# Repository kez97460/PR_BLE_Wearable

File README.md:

# Projet de recherche - beacon BLE wearable

Projet de recherche de Lïam Lotte et Kézia Marcou - mineure E&E. 

Vous trouverez le rapport du projet en .pdf à ce [lien](project_report.pdf).

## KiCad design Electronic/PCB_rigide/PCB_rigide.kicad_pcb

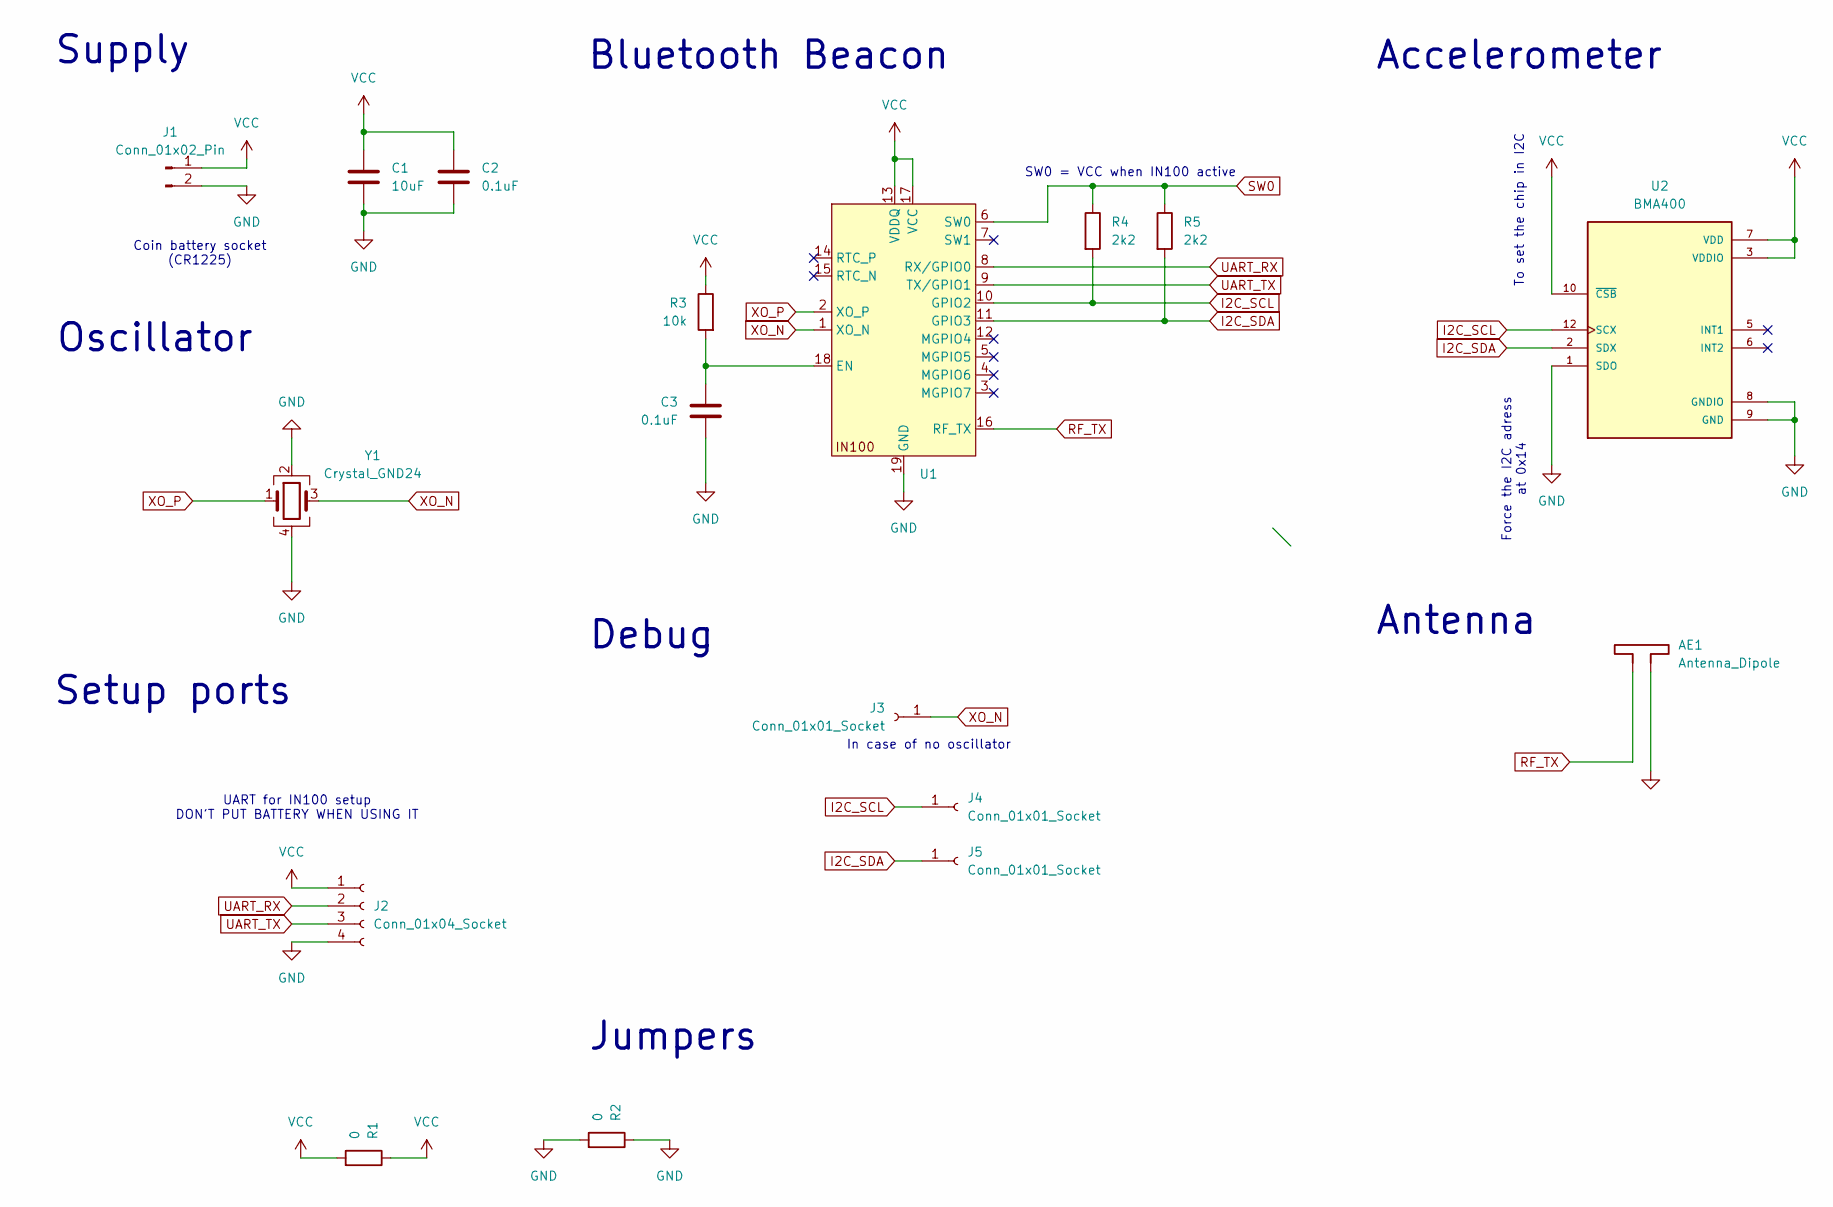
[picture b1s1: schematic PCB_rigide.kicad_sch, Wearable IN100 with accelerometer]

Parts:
AE1: Antenna_Dipole; Texas_SWRA117D_2.4GHz_Left
C1: 10uF; C_1206_3216Metric_Pad1.33x1.80mm_HandSolder
C2, C3: 0.1uF; C_1206_3216Metric_Pad1.33x1.80mm_HandSolder
J1: Conn_01x02_Pin; PinSocket_1x02_P2.54mm_Vertical
J2: Conn_01x04_Socket; PinSocket_1x04_P2.54mm_Vertical
J3, J4, J5: Conn_01x01_Socket; TestPoint_Loop_D2.54mm_Drill1.5mm_Beaded
R1, R2: 0; R_1206_3216Metric
R3: 10k; R_1206_3216Metric
R4, R5: 2k2; R_1206_3216Metric
U1: QFN19P40_300X300X80L35X20T170X150N
U2: BMA400; XDCR_BMA400; DigiKey_Part_Number 828-1081-2-ND
Y1: Crystal_GND24; Crystal_SMD_2016-4Pin_2.0x1.6mm

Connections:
GND: AE1.2, C1.2, C2.2, C3.2, J1.2, J2.4, R2.1, R2.2, U1.19 (GND), U2.1 (SDO), U2.8 (GNDIO), U2.9 (GND), Y1.2, Y1.4
I2C_SCL: J4.1, R4.2, U1.10 (GPIO2), U2.12 (SCX)
I2C_SDA: J5.1, R5.2, U1.11 (GPIO3), U2.2 (SDX)
unnamed: C3.1, R3.2, U1.18 (EN)
RF_TX: AE1.1, U1.16 (RF_TX)
SW0: R4.1, R5.1, U1.6 (SW0)
UART_RX: J2.2, U1.8 (RX/GPIO0)
UART_TX: J2.3, U1.9 (TX/GPIO1)
VCC: C1.1, C2.1, J1.1, J2.1, R1.1, R1.2, R3.1, U1.13 (VDDQ), U1.17 (VCC), U2.3 (VDDIO), U2.7 (VDD), U2.10 (~CSB)
XO_N: J3.1, U1.1 (XO_N), Y1.3
XO_P: U1.2 (XO_P), Y1.1

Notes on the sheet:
Accelerometer
In case of no oscillator
Debug
Antenna
Supply
Coin battery socket (CR1225)
UART for IN100 setup DON'T PUT BATTERY WHEN USING IT
Setup ports
Oscillator
Jumpers
To set the chip in I2C
Bluetooth Beacon
SW0 = VCC when IN100 active
Force the I2C adress at 0x14

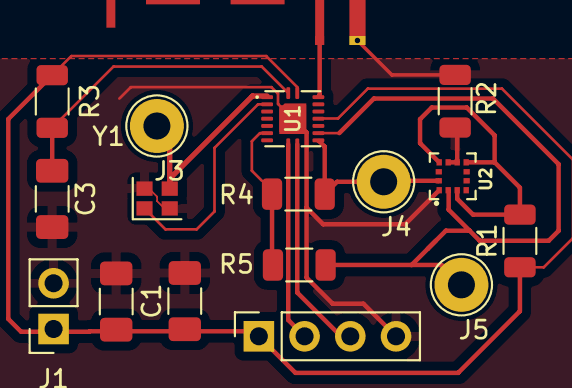
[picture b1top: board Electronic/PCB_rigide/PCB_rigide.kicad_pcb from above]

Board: 2 copper layers, 17 parts (0 on the bottom side), 11 nets.

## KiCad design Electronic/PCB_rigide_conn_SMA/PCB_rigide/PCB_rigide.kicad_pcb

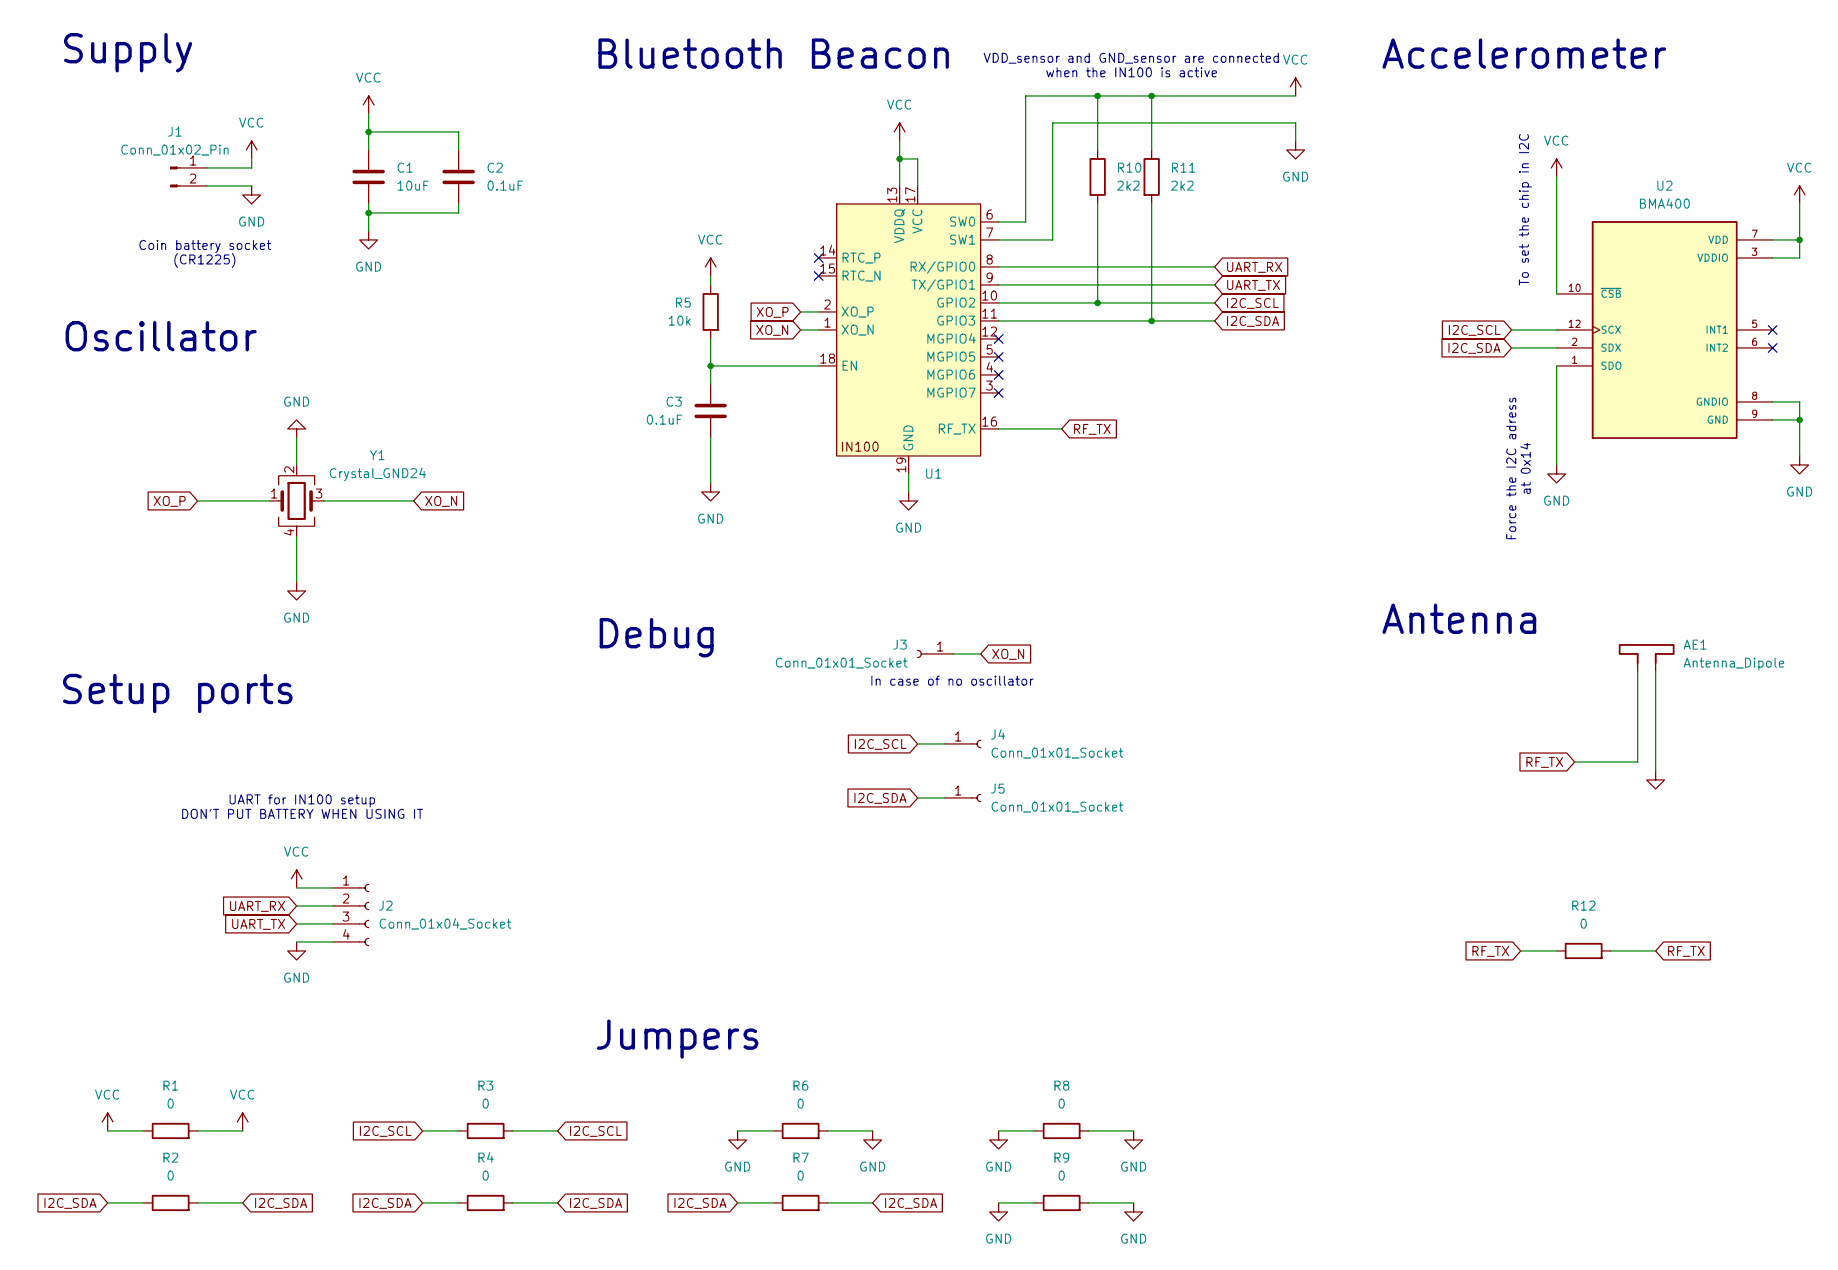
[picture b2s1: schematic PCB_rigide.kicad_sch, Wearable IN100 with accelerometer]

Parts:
AE1: Antenna_Dipole; Texas_SWRA117D_2.4GHz_Right
C1: 10uF; C_1206_3216Metric_Pad1.33x1.80mm_HandSolder
C2, C3: 0.1uF; C_1206_3216Metric_Pad1.33x1.80mm_HandSolder
J1: Conn_01x02_Pin; PinSocket_1x02_P2.54mm_Vertical
J2: Conn_01x04_Socket; PinSocket_1x04_P2.54mm_Vertical
J3, J4, J5: Conn_01x01_Socket; TestPoint_Loop_D2.54mm_Drill1.5mm_Beaded
R1, R2, R3, R4, R6, R7, R8, R9, R12: 0; R_1206_3216Metric
R5: 10k; R_1206_3216Metric
R10, R11: 2k2; R_1206_3216Metric
U1: QFN19P40_300X300X80L35X20T170X150N
U2: BMA400; XDCR_BMA400; DigiKey_Part_Number 828-1081-2-ND
Y1: Crystal_GND24; Crystal_SMD_3225-4Pin_3.2x2.5mm_HandSoldering

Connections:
GND: AE1.2, C1.2, C2.2, C3.2, J1.2, J2.4, R6.1, R6.2, R8.1, R8.2, R9.1, R9.2, U1.7 (SW1), U1.19 (GND), U2.1 (SDO), U2.8 (GNDIO), U2.9 (GND), Y1.2, Y1.4
I2C_SCL: J4.1, R3.1, R3.2, R10.2, U1.10 (GPIO2), U2.12 (SCX)
I2C_SDA: J5.1, R2.1, R2.2, R4.1, R4.2, R7.1, R7.2, R11.2, U1.11 (GPIO3), U2.2 (SDX)
unnamed: C3.1, R5.2, U1.18 (EN)
RF_TX: AE1.1, R12.1, R12.2, U1.16 (RF_TX)
UART_RX: J2.2, U1.8 (RX/GPIO0)
UART_TX: J2.3, U1.9 (TX/GPIO1)
VCC: C1.1, C2.1, J1.1, J2.1, R1.1, R1.2, R5.1, R10.1, R11.1, U1.6 (SW0), U1.13 (VDDQ), U1.17 (VCC), U2.3 (VDDIO), U2.7 (VDD), U2.10 (~CSB)
XO_N: J3.1, U1.1 (XO_N), Y1.3
XO_P: U1.2 (XO_P), Y1.1

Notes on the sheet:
Accelerometer
In case of no oscillator
Debug
Antenna
Supply
Coin battery socket (CR1225)
UART for IN100 setup DON'T PUT BATTERY WHEN USING IT
Setup ports
Oscillator
Jumpers
VDD_sensor and GND_sensor are connected when the IN100 is active
To set the chip in I2C
Bluetooth Beacon
Force the I2C adress at 0x14

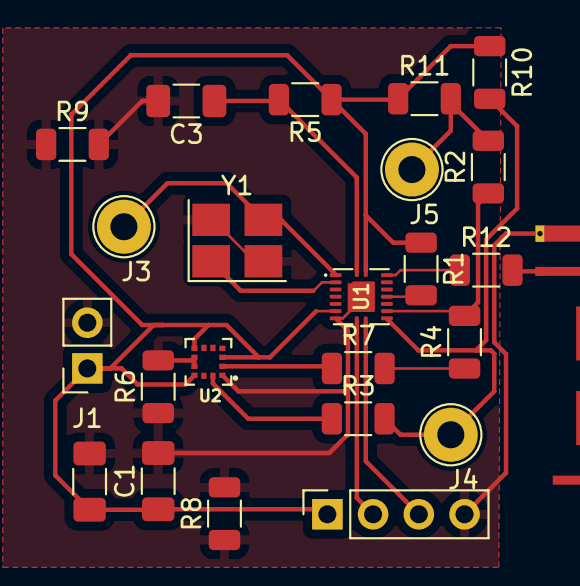
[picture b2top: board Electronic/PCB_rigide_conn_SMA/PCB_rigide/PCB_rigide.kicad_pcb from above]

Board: 2 copper layers, 24 parts (0 on the bottom side), 10 nets.

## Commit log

2025-03-05 python recup Vcc OK
2025-03-06 appli web affichage Vcc
2025-03-07 save before i break smth
2025-03-07 retiré code inutile
2025-03-07 week end (update README)
2025-03-10 ok with fake data
2025-03-10 init elec
2025-03-11 mostly OK
2025-03-11 a bit of cleanup
2025-03-11 deleted useless code
2025-03-11 updated requirements with the actual versions
2025-03-14 app should be OK, documented
2025-03-14 delattre explication
2025-03-25 update electronic
2025-03-25 Arduino simu IN100 OK
2025-03-25 add low power mode
2025-03-25 IN100_Configs
2025-03-26 updated python code
2025-03-27 final push
